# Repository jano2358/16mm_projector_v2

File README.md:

# 16mm_projector_v2
mod of a 16mm projector for the project "El curso del tiempo" from Xavi Hurtado

This is a modification of a projector (EIKI SSL0L) to take control over the parameters of the projection: tape speed, amount of light and shutter.
For the light we replace the incandescent bulb (300W, lumens: unknown)  by a COB LED (Citizen CLU058-1825C4-303M2K1, 100W about 17000 lumen).
To control the tape speed, We replaced the original motor with a DC brushless servo motor (Trinamic QBL5704-94-04-032 and TMCM-1630 control board).
The shutter originaly was hard linked to the main motor, we eliminated the hard link to have control independant, added a secondary shutter and two DC motors to move them. The link to the main motor and sync was made by a dual PLL system programed on an Arduino M0 board.
The power for these DC motors is delivered trough a Pololu board dual MC33296.
Arduino also controls the communication with the TMCM-1630 trough serial interface, the amount of light by switching the LED with a power
mosfet and receive the control from the computer over an ethernet line in OSC packets (we use here the Arduino Ethernet 2 Wiznet W5500).
The power is supplied by a Mean Well RSP-500-48 raised to 54V, with two DC-DC converters based on the TPS54560 chip from TI.

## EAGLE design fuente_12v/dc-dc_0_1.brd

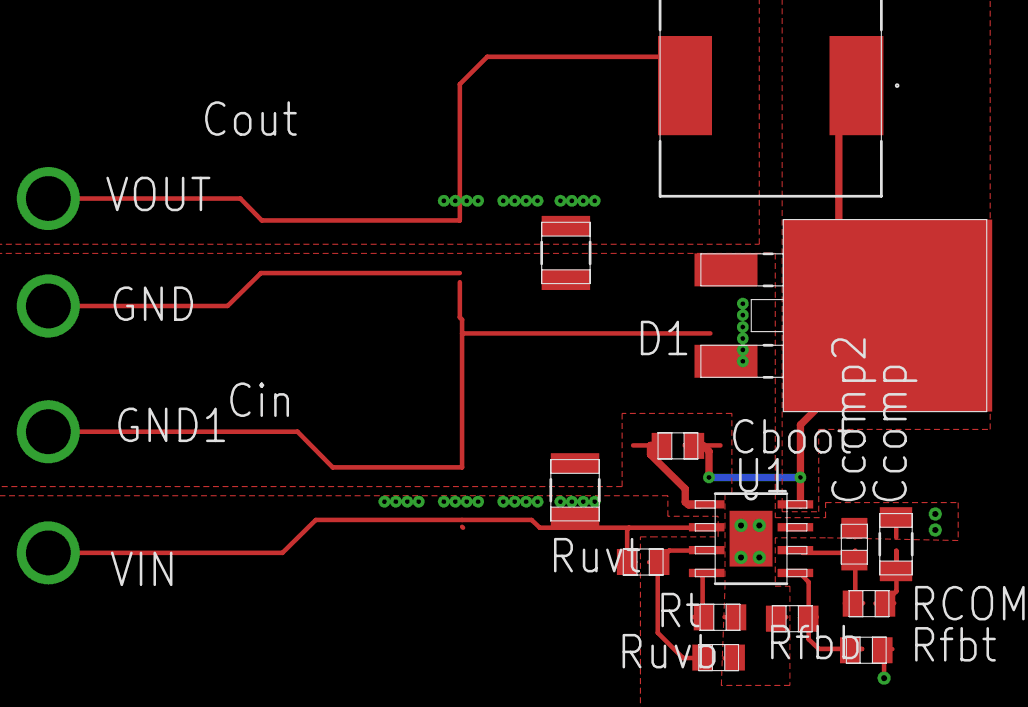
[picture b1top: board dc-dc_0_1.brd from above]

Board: 4 copper layers, 18 parts (0 on the bottom side), 10 nets.

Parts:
Cboot: 0805
Ccomp: 1206
Ccomp2: 0805
Cin: 1210
Cout: 1210_280
D1: DDPAK
GND, GND1: TP-1502
L1: MSS1210
RCOMP: 0805
Rfbb: 0805
Rfbt: 0805
Rt: 0805
Ruvb: 0805
Ruvt: 0805
U1: R-PDSO-G8
VIN: TP-1502
VOUT: TP-1502

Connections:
0: Ccomp.2, Ccomp2.2, Cin.2, Cout.2, D1.1, D1.3, GND.1, GND1.1, Rfbb.2, Rt.2, Ruvb.2, U1.7, U1.9
1: Ccomp2.1, RCOMP.2, U1.6
2: Rt.1, U1.4
3: Cboot.1, U1.1
4: Rfbb.1, Rfbt.2, U1.5
5: Cboot.2, D1.2, L1.1, U1.8
6: Cin.1, Ruvt.1, U1.2, VIN.1
7: Cout.1, L1.2, Rfbt.1, VOUT.1
20: Ccomp.1, RCOMP.1
29: Ruvb.1, Ruvt.2, U1.3

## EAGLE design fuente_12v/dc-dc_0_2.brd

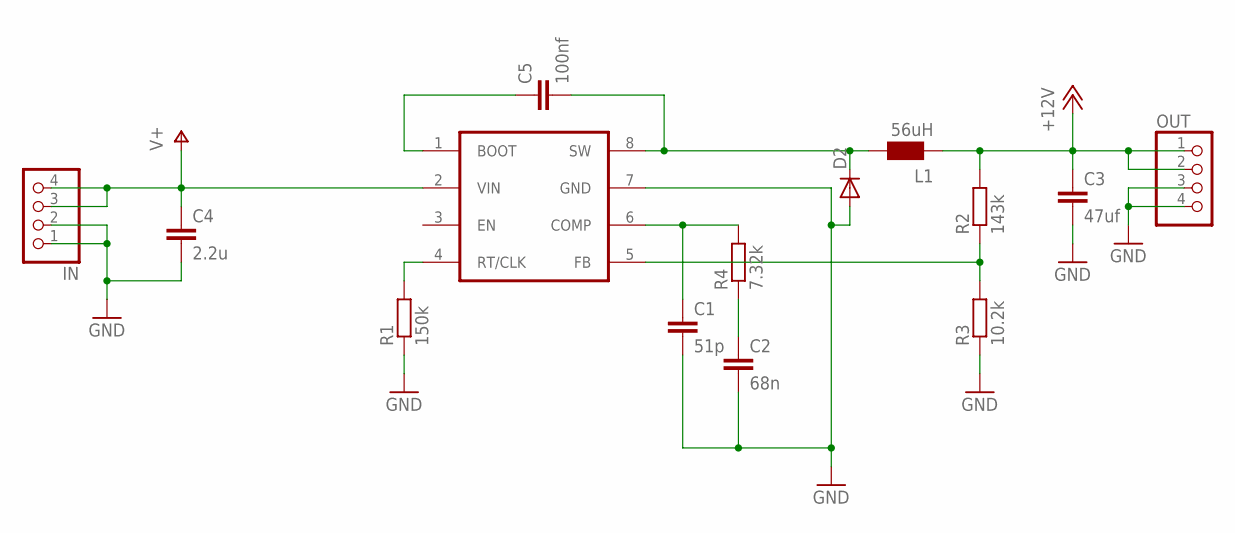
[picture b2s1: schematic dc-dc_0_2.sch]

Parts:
C1: 51p; C0805
C2: 68n; C1206
C3: 47uf; C1210
C4: 2.2u; C1210
C5: 100nf; C0805
D2: DIODE-DO-214AC; DO-214AC
IN: PINHD-1X4; 1X04
L1: 56uH; WE-PD_L/XL/XXL
OUT: PINHD-1X4; 1X04
R1: 150k; R0805
R2: 143k; R0805
R3: 10.2k; R0805
R4: 7.32k; R0805
U1: TPS54560; SO08-POWERPAD

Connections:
+12V: C3.1, L1.2 (1), OUT.1, OUT.2, R2.2
GND: C1.2, C2.2, C3.2, C4.2, D2.A, IN.1, IN.2, OUT.3, OUT.4, R1.1, R3.1, U1.7 (GND)
unnamed: C5.1, U1.1 (BOOT)
unnamed: C5.2, D2.C, L1.1 (2), U1.8 (SW)
unnamed: R2.1, R3.2, U1.5 (FB)
unnamed: C1.1, R4.2, U1.6 (COMP)
unnamed: C2.1, R4.1
unnamed: R1.2, U1.4 (RT/CLK)
V+: C4.1, IN.3, IN.4, U1.2 (VIN)

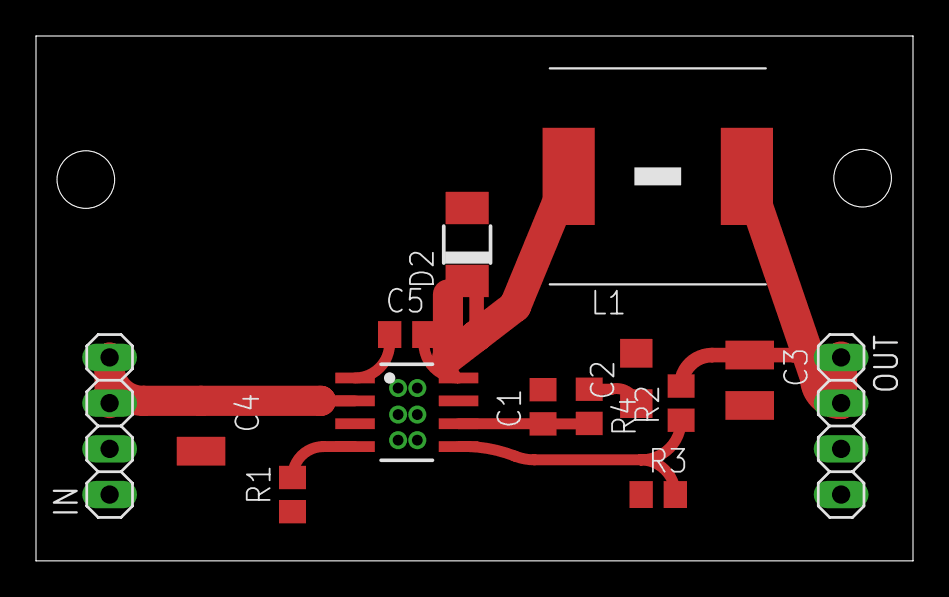
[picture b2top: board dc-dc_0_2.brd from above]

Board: 2 copper layers, 48.7 x 29.2 mm, 14 parts (0 on the bottom side), 9 nets.

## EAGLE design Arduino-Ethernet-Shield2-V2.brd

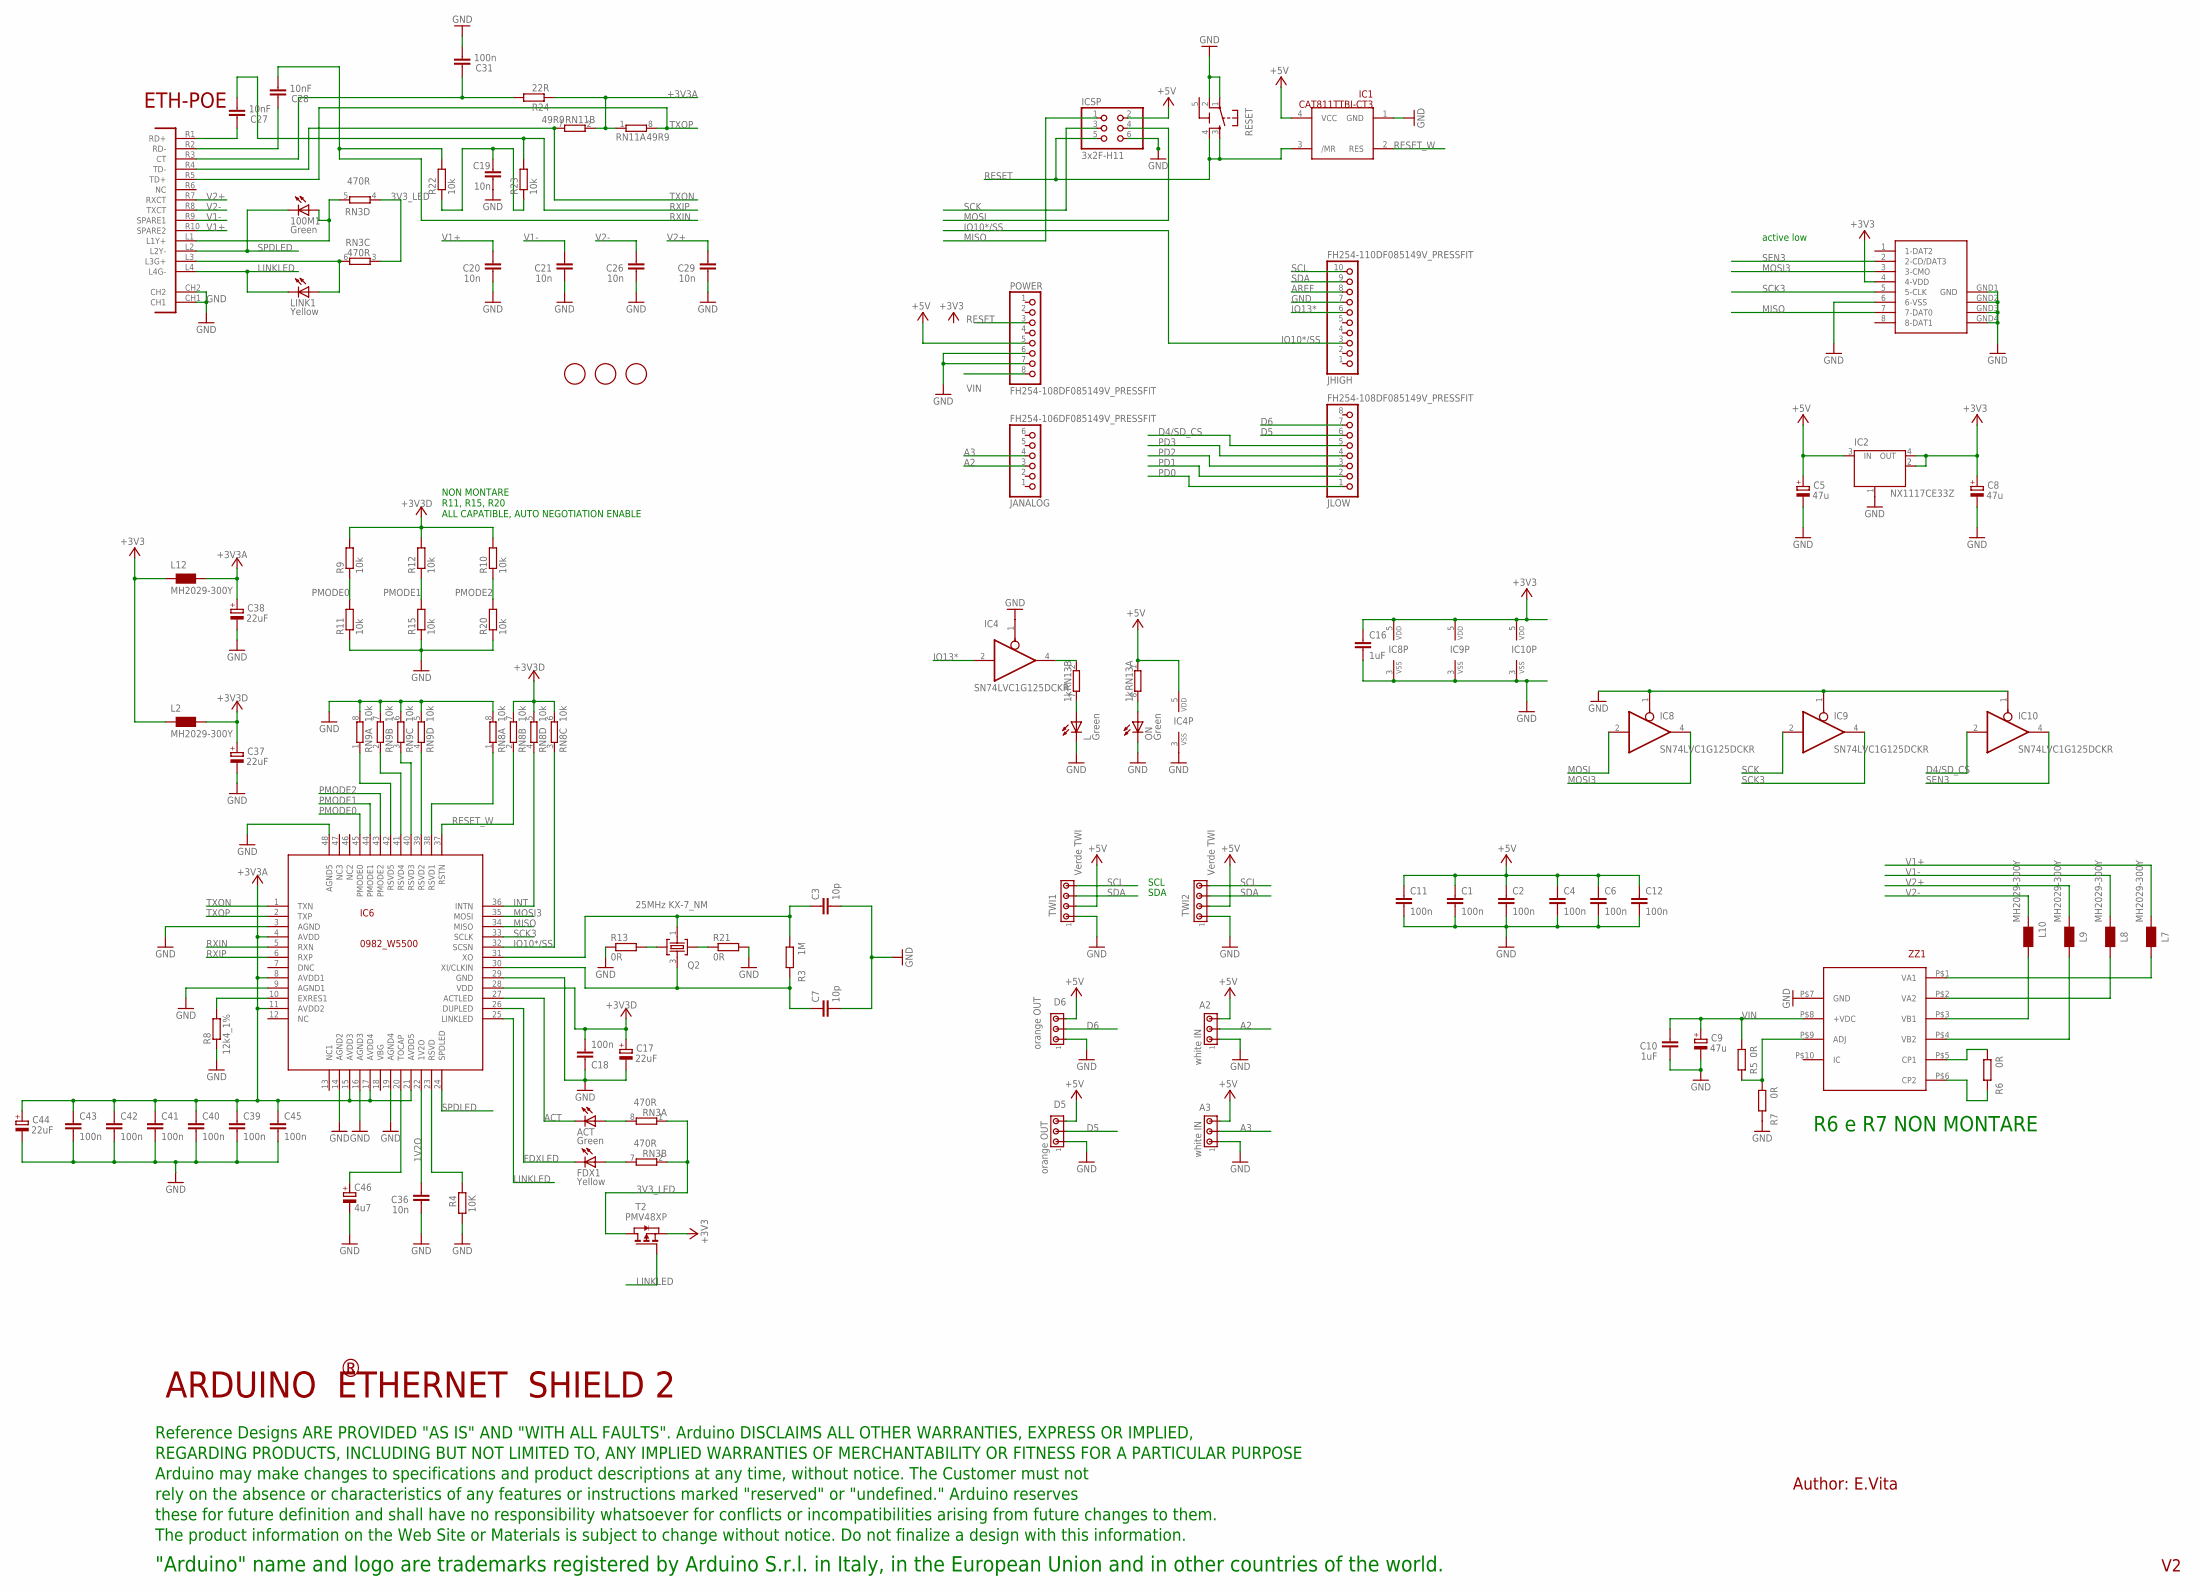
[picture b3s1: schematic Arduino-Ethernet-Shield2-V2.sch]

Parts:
100M1: Green; CHIPLED_0805
A2, A3: white IN; 10X03MTA
ACT: Green; CHIPLED_0805
C1, C2, C4, C6, C11, C12, C18, C31, C39, C40, C41, C42, C43, C45: 100n; C0603-ROUND
C3, C7: 10p; C0603-ROUND
C5, C8, C9: 47u; PANASONIC_D
C10, C16: 1uF; C0603-ROUND
C17, C37, C38, C44: 22uF; SMC_B
C19, C20, C21, C26, C29, C36: 10n; C0603-ROUND
C27, C28: 10nF; C0603-ROUND
C46: 4u7; SMC_A
D5, D6: orange OUT; 10X03MTA
FDX1: Yellow; CHIPLED_0805
FID2, FID3, FID4: FIDUCIALMOUNT; FIDUCIA-MOUNT
IC1: CAT811TTBI-CT3; SOT143
IC2: NX1117CE33Z; SOT223
IC4, IC8, IC9, IC10: SN74LVC1G125DCKR; SC70-5
IC6: 0982_W5500; TQFP48-7X7
ICSP: 3x2F-H11; 2X03
JANALOG: FH254-106DF085149V_PRESSFIT; 1X06-TH-PRESSFIT
JHIGH: FH254-110DF085149V_PRESSFIT; 1X10-TH-PRESSFIT
JLOW: FH254-108DF085149V_PRESSFIT; 1X08-TH-PRESSFIT
L: Green; CHIPLED_0805
L2, L7, L8, L9, L10, L12: MH2029-300Y; 0805
LINK1: Yellow; CHIPLED_0805
ON: Green; CHIPLED_0805
POWER: FH254-108DF085149V_PRESSFIT; 1X08-TH-PRESSFIT
Q2: 25MHz KX-7_NM; CRYSTAL3.2X2.5
R3: 1M; R0603-ROUND
R4: 10K; R0603-ROUND
R5, R6, R7: 0R; R0603-ROUND
R8: 12k4_1%; R0603-ROUND
R9, R10, R11, R12, R15, R20, R22, R23: 10k; R0603-ROUND
R13, R21: 0R; R0402
R24: 22R; R0603-ROUND
RESET: 0946_TS42031-160W-TR-7260; TS42
RN3: 470R; CAY16
RN8, RN9: 10k; CAY16
RN11: 49R9; CAY16
RN13: 1k; CAY16
T2: PMV48XP; SOT-23; PART_NUMBER PMV48XP
TWI1, TWI2: Verde TWI; 10X04MTA
U$1: DISCLAIMER
UC1: RB1-125BHQ1A; POE-RJ45
X1: 0046_15TW-882; SDCARD-15TW-8821
ZZ1: 0343_AG9612-2BR; AG9000

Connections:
1V2O: C36.2, IC6.22 (1V2O)
3V3_LED: RN3.1, RN3.2 (1), RN3.3 (1), RN3.4 (1), T2.1 (D)
5-GND: RESET.5 (5-GND)
+3V3: C8.+, C16.1, IC2.2 (OUT), IC2.4 (OUT), IC8.5 (VDD), IC9.5 (VDD), IC10.5 (VDD), L2.1, L12.1, T2.2 (S), X1.4 (4-VDD)
+3V3A: C38.+, C39.1, C40.1, C41.1, C42.1, C43.1, C44.+, C45.1, IC6.4 (AVDD), IC6.8 (AVDD1), IC6.11 (AVDD2), IC6.15 (AVDD3), IC6.17 (AVDD4), IC6.21 (AVDD5), L12.2, R24.1, RN11.1, RN11.2 (1)
+3V3D: C17.+, C18.2, C37.+, IC6.28 (VDD), L2.2, R9.2, R10.2, R12.2, RN8.5 (2), RN8.6 (2), RN8.7 (2)
+5V: A2.3, A3.3, C1.1, C2.1, C4.1, C5.+, C6.1, C11.1, C12.1, D5.3, D6.3, IC1.4 (VCC), IC2.3 (IN), IC4.5 (VDD), ICSP.2, POWER.5, RN13.1, TWI1.2, TWI2.2
A2: A2.2, JANALOG.3
A3: A3.2, JANALOG.4
ACT: ACT.C, IC6.27 (ACTLED)
AREF: JHIGH.8
D4/SD_CS: IC10.2 (I), JLOW.5
D5: D5.2, JLOW.6
D6: D6.2, JLOW.7
FDXLED: FDX1.C, IC6.26 (DUPLED)
GND: A2.1, A3.1, C1.2, C2.2, C3.2, C4.2, C5.-, C6.2, C7.2, C8.-, C9.-, C10.1, C11.2, C12.2, C16.2, C17.-, C18.1, C19.1, C20.1, C21.1, C26.1, C29.1, C31.1, C36.1, C37.-, C38.-, C39.2, C40.2, C41.2, C42.2, C43.2, C44.-, C45.2, C46.-, D5.1, D6.1, IC1.1 (GND), IC2.1 (GND/ADJ), IC4.1 (OE), IC4.3 (VSS), IC6.3 (AGND), IC6.9 (AGND1), IC6.14 (AGND2), IC6.16 (AGND3), IC6.19 (AGND4), IC6.29 (GND), IC6.48 (AGND5), IC8.1 (OE), IC8.3 (VSS), IC9.1 (OE), IC9.3 (VSS), IC10.1 (OE), IC10.3 (VSS), ICSP.6, JHIGH.7, L.C, ON.C, POWER.6, POWER.7, R4.1, R7.2, R8.1, R11.1, R13.1, R15.1, R20.1, R21.2, RESET.1, RESET.2, RN8.8 (2), RN9.5 (2), RN9.6 (2), RN9.7 (2), RN9.8 (2), TWI1.1, TWI2.1, UC1.CH1, UC1.CH2, X1.6 (6-VSS), X1.GND1 (GND), X1.GND2 (GND1), X1.GND3 (GND2), X1.GND4 (GND3), ZZ1.P$7 (GND)
INT: IC6.36 (INTN), RN8.4 (1)
IO10*/SS: IC6.32 (SCSN), JHIGH.3, RN8.3 (1)
IO13*: IC4.2 (I), JHIGH.6
LINKLED: IC6.25 (LINKLED), LINK1.C, T2.3 (G), UC1.L4 (L4G-)
MISO: IC6.34 (MISO), ICSP.1, X1.7 (7-DAT0)
MOSI: IC8.2 (I), ICSP.4
MOSI3: IC6.35 (MOSI), IC8.4 (O), X1.3 (3-CMO)
unnamed: L7.2, ZZ1.P$1 (VA1)
unnamed: L8.2, ZZ1.P$2 (VA2)
unnamed: L9.2, ZZ1.P$4 (VB2)
unnamed: L10.2, ZZ1.P$3 (VB1)
unnamed: C3.1, IC6.31 (XO), Q2.1, R3.1
unnamed: IC6.39 (RSVD2), RN9.4 (1)
unnamed: ACT.A, RN3.8 (2)
unnamed: Q2.2, R13.2
unnamed: Q2.4, R21.1
unnamed: LINK1.A, RN3.6 (2), UC1.L3 (L3G+)
unnamed: IC6.23 (RSVD), R4.2
unnamed: 100M1.A, RN3.5 (2), UC1.L1 (L1Y+)
unnamed: C19.2, R22.1, R23.1
unnamed: C27.2, UC1.R1 (RD+)
unnamed: C28.2, UC1.R2 (RD-)
unnamed: FDX1.A, RN3.7 (2)
unnamed: IC6.40 (RSVD3), RN9.3 (1)
unnamed: R6.1, ZZ1.P$5 (CP1)
unnamed: R6.2, ZZ1.P$6 (CP2)
unnamed: R5.2, R7.1, ZZ1.P$9 (ADJ)
unnamed: IC6.41 (RSVD4), RN9.2 (1)
unnamed: C31.2, R24.2, UC1.R3 (CT)
unnamed: IC6.42 (RSVD5), RN9.1
unnamed: C46.+, IC6.20 (TOCAP)
unnamed: IC6.38 (RSVD1), RN8.1
unnamed: IC6.10 (EXRES1), R8.2
unnamed: ON.A, RN13.8 (2)
unnamed: IC4.4 (O), RN13.2 (1)
unnamed: L.A, RN13.7 (2)
NC: IC6.12 (NC)
OSC2E2: C7.1, IC6.30 (XI/CLKIN), Q2.3, R3.2
PD0: JLOW.1
PD1: JLOW.2
PD2: JLOW.3
PD3: JLOW.4
PMODE0: IC6.45 (PMODE0), R9.1, R11.2
PMODE1: IC6.44 (PMODE1), R12.1, R15.2
PMODE2: IC6.43 (PMODE2), R10.1, R20.2
RESET: IC1.3 (/MR), ICSP.5, POWER.3, RESET.3, RESET.4
RESET_W: IC1.2 (RES), IC6.37 (RSTN), RN8.2 (1)
RXIN: C28.1, IC6.5 (RXN), R22.2
RXIP: C27.1, IC6.6 (RXP), R23.2
SCK: IC9.2 (I), ICSP.3
SCK3: IC6.33 (SCLK), IC9.4 (O), X1.5 (5-CLK)
SCL: JHIGH.10, TWI1.4, TWI2.4
SDA: JHIGH.9, TWI1.3, TWI2.3
SEN3: IC10.4 (O), X1.2 (2-CD/DAT3)
SPDLED: 100M1.C, IC6.24 (SPDLED), UC1.L2 (L2Y-)
TXON: IC6.1 (TXN), RN11.7 (2), UC1.R4 (TD-)
TXOP: IC6.2 (TXP), RN11.8 (2), UC1.R5 (TD+)
V1+: C20.2, L7.1, UC1.R10 (SPARE2)
V1-: C21.2, L8.1, UC1.R9 (SPARE1)
V2+: C29.2, L9.1, UC1.R7 (RXCT)
V2-: C26.2, L10.1, UC1.R8 (TXCT)
VIN: C9.+, C10.2, POWER.8, R5.1, ZZ1.P$8 (+VDC)

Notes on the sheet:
active low
NON MONTARE R11, R15, R20 ALL CAPATIBLE, AUTO NEGOTIATION ENABLE
ETH-POE
SCL
SDA
R6 e R7 NON MONTARE
ARDUINO ETHERNET SHIELD 2
Author: E.Vita

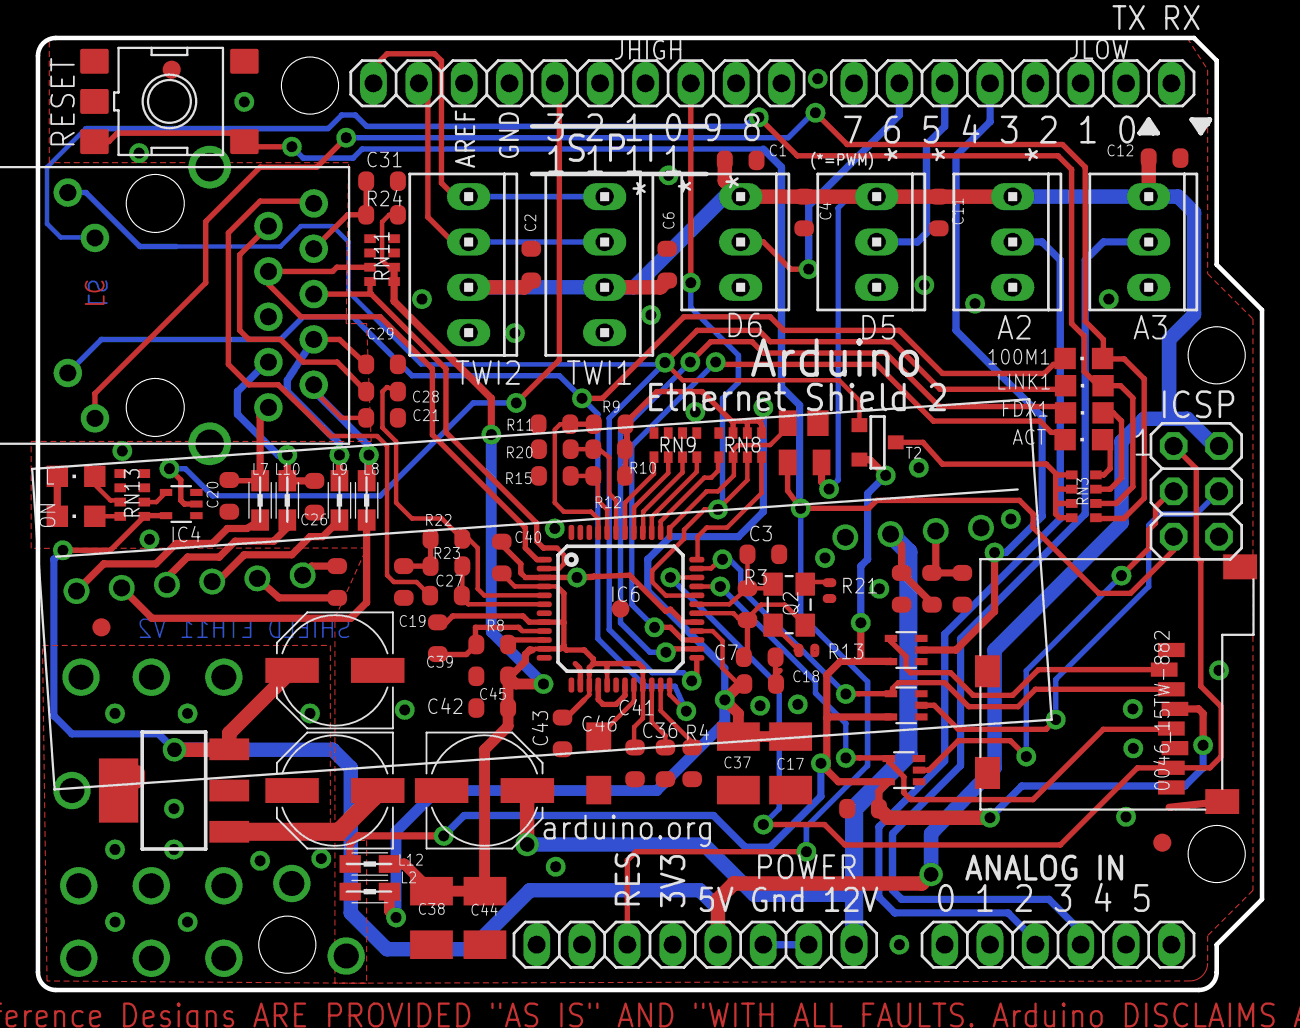
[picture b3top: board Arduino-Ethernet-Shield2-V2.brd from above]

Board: 2 copper layers, 68.6 x 53.3 mm, 96 parts (0 on the bottom side), 71 nets.

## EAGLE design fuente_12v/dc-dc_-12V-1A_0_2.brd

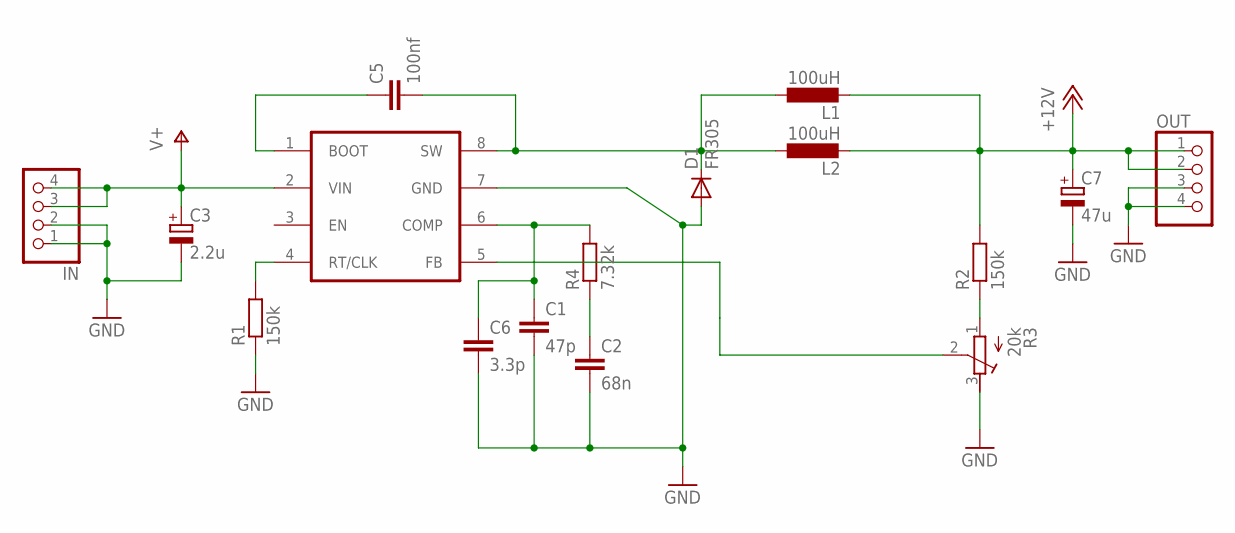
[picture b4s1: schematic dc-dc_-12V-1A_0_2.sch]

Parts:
C1: 47p; C1206
C2: 68n; C1206
C3: 2.2u; E2-4
C5: 100nf; C0805
C6: 3.3p; C1206
C7: 47u; E2-4
D1: FR305; DO201-15
IN: PINHD-1X4; 1X04
L1, L2: 100uH; RCL_6000-XXXX-RC
OUT: PINHD-1X4; 1X04
R1, R2: 150k; R0805
R3: 20k; RTRIM64X
R4: 7.32k; 0204/5
U1: TPS54560; SO08-POWERPAD

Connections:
+12V: C7.+, L1.2, L2.2, OUT.1, OUT.2, R2.2
GND: C1.2, C2.2, C3.-, C6.2, C7.-, D1.A, IN.1, IN.2, OUT.3, OUT.4, R1.1, R3.3 (A), U1.7 (GND)
unnamed: C5.1, U1.1 (BOOT)
unnamed: C5.2, D1.C, L1.1, L2.1, U1.8 (SW)
unnamed: R2.1, R3.1 (E)
unnamed: R3.2 (S), U1.5 (FB)
unnamed: C1.1, C6.1, R4.2, U1.6 (COMP)
unnamed: C2.1, R4.1
unnamed: R1.2, U1.4 (RT/CLK)
V+: C3.+, IN.3, IN.4, U1.2 (VIN)

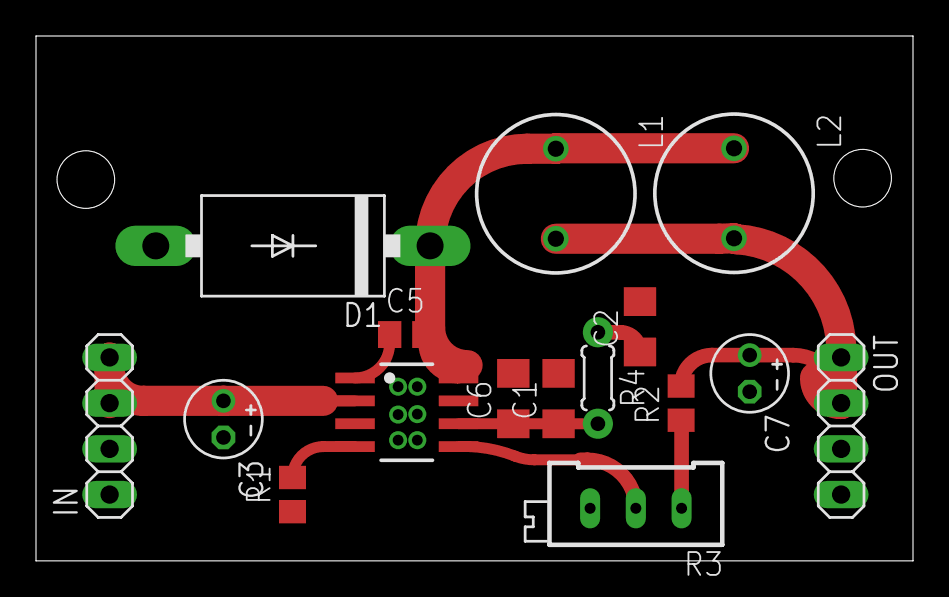
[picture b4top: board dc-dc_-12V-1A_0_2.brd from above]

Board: 2 copper layers, 48.7 x 29.2 mm, 16 parts (0 on the bottom side), 10 nets.

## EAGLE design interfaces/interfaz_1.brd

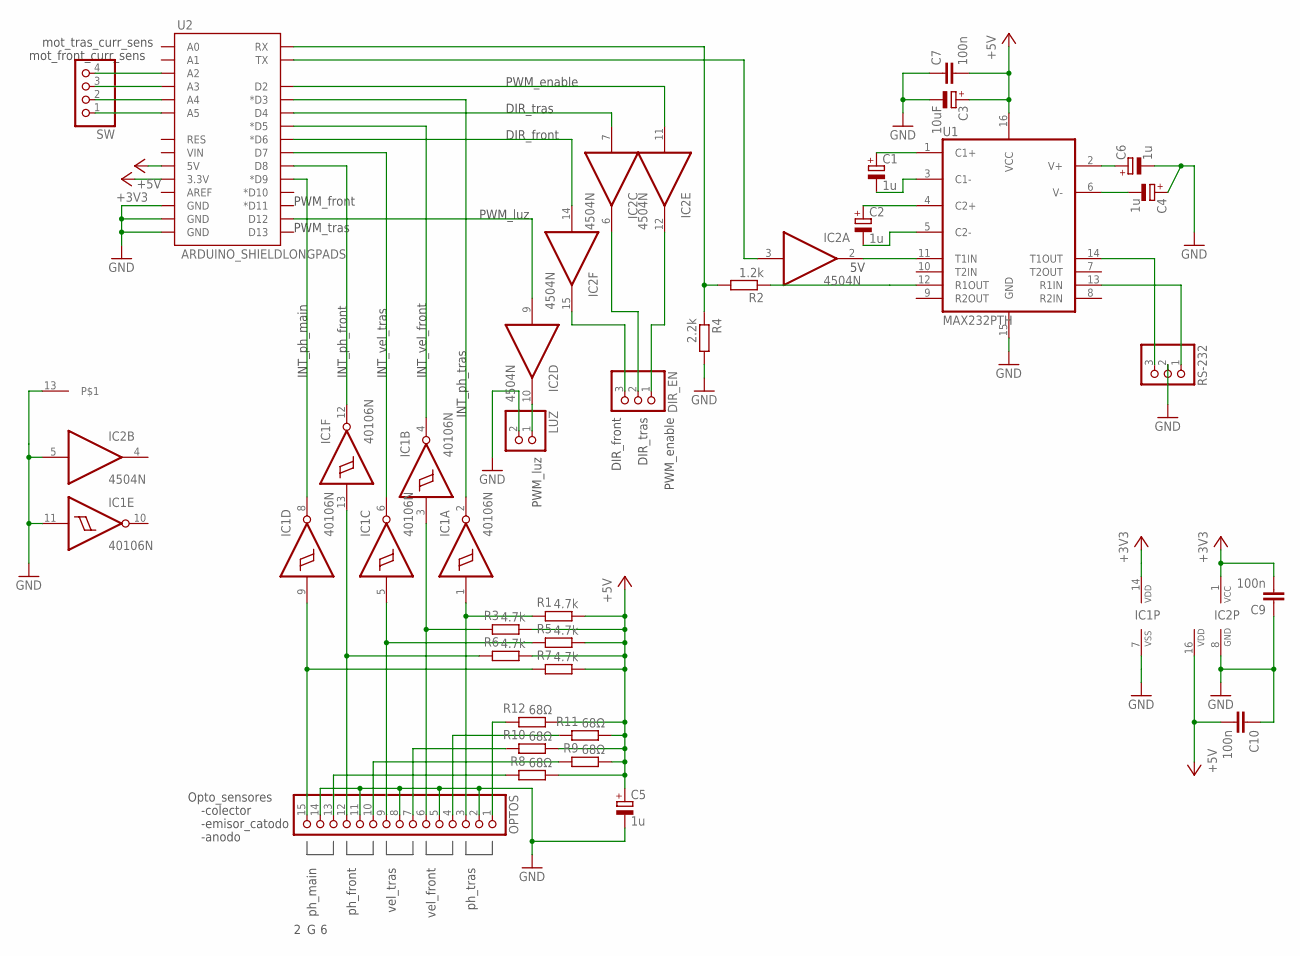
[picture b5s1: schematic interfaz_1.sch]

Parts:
C1, C2, C4, C5, C6: 1u; E2-4
C3: 10uF; E2-4
C7, C9, C10: 100n; C025-025X050
DIR_EN: PINHD-1X3; 1X03
IC1: 40106N; DIL14
IC2: 4504N; DIL16
LUZ: PINHD-1X2; 1X02
OPTOS: PINHD-1X15; 1X15
R1, R3, R5, R6, R7: 4.7k; 0204/5
R2: 1.2k; 0204/5
R4: 2.2k; 0204/5
R8, R9, R10, R11, R12: 68Ω; 0204/5
RS-232: PINHD-1X3; 1X03
SW: PINHD-1X4; 1X04
U1: MAX232PTH; DIL16
U2: ARDUINO_SHIELDLONGPADS; DUEMILANOVE_SHIELD_LONGPADS

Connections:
+3V3: C9.2, IC1.14 (VDD), IC2.1 (VCC), U2.3.3V
+5V: C3.+, C5.+, C7.2, C10.2, IC2.16 (VDD), R1.1, R3.1, R5.1, R6.1, R7.1, R8.1, R9.1, R10.1, R11.1, R12.1, U1.16 (VCC), U2.5V
GND: C3.-, C4.+, C5.-, C6.-, C7.1, C9.1, C10.1, IC1.7 (VSS), IC1.11 (I), IC2.5 (I), IC2.8 (GND), IC2.13, LUZ.2, OPTOS.2, OPTOS.5, OPTOS.8, OPTOS.11, OPTOS.14, R4.2, RS-232.2, U1.15 (GND), U2.GND@0 (GND), U2.GND@1 (GND), U2.GND@2 (GND)
unnamed: C1.+, U1.1 (C1+)
unnamed: C1.-, U1.3 (C1-)
unnamed: C2.+, U1.4 (C2+)
unnamed: C2.-, U1.5 (C2-)
unnamed: C4.-, U1.6 (V-)
unnamed: C6.+, U1.2 (V+)
unnamed: RS-232.1, U1.13 (R1IN)
unnamed: IC2.11 (I), U2.D2
unnamed: IC2.3 (I), U2.TX
unnamed: R2.1, U1.12 (R1OUT)
unnamed: R2.2, R4.1, U2.RX
unnamed: IC2.2 (O), U1.11 (T1IN)
unnamed: DIR_EN.1, IC2.12 (O)
unnamed: RS-232.3, U1.14 (T1OUT)
unnamed: IC2.7 (I), U2.D4
unnamed: DIR_EN.2, IC2.6 (O)
unnamed: IC2.14 (I), U2.D6 (*D6)
unnamed: DIR_EN.3, IC2.15 (O)
unnamed: IC2.9 (I), U2.D12
unnamed: IC2.10 (O), LUZ.1
unnamed: IC1.3 (I), OPTOS.6, R3.2
unnamed: IC1.2 (O), U2.D3 (*D3)
unnamed: IC1.4 (O), U2.D5 (*D5)
unnamed: IC1.6 (O), U2.D7
unnamed: IC1.12 (O), U2.D8
unnamed: IC1.8 (O), U2.D9 (*D9)
unnamed: IC1.1 (I), OPTOS.3, R1.2
unnamed: IC1.5 (I), OPTOS.9, R5.2
unnamed: IC1.13 (I), OPTOS.12, R6.2
unnamed: IC1.9 (I), OPTOS.15, R7.2
unnamed: OPTOS.13, R8.2
unnamed: OPTOS.10, R9.2
unnamed: OPTOS.7, R10.2
unnamed: OPTOS.4, R11.2
unnamed: OPTOS.1, R12.2
unnamed: SW.1, U2.A5
unnamed: SW.2, U2.A4
unnamed: SW.3, U2.A3
unnamed: SW.4, U2.A2

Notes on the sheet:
PWM_enable
DIR_tras
DIR_front
PWM_luz
PWM_tras
PWM_front
INT_vel_tras
INT_vel_front
INT_ph_tras
INT_ph_front
INT_ph_main
Opto_sensores
-colector
-emisor_catodo
-anodo
ph_main
ph_front
ph_tras
vel_front
vel_tras
mot_tras_curr_sens
mot_front_curr_sens

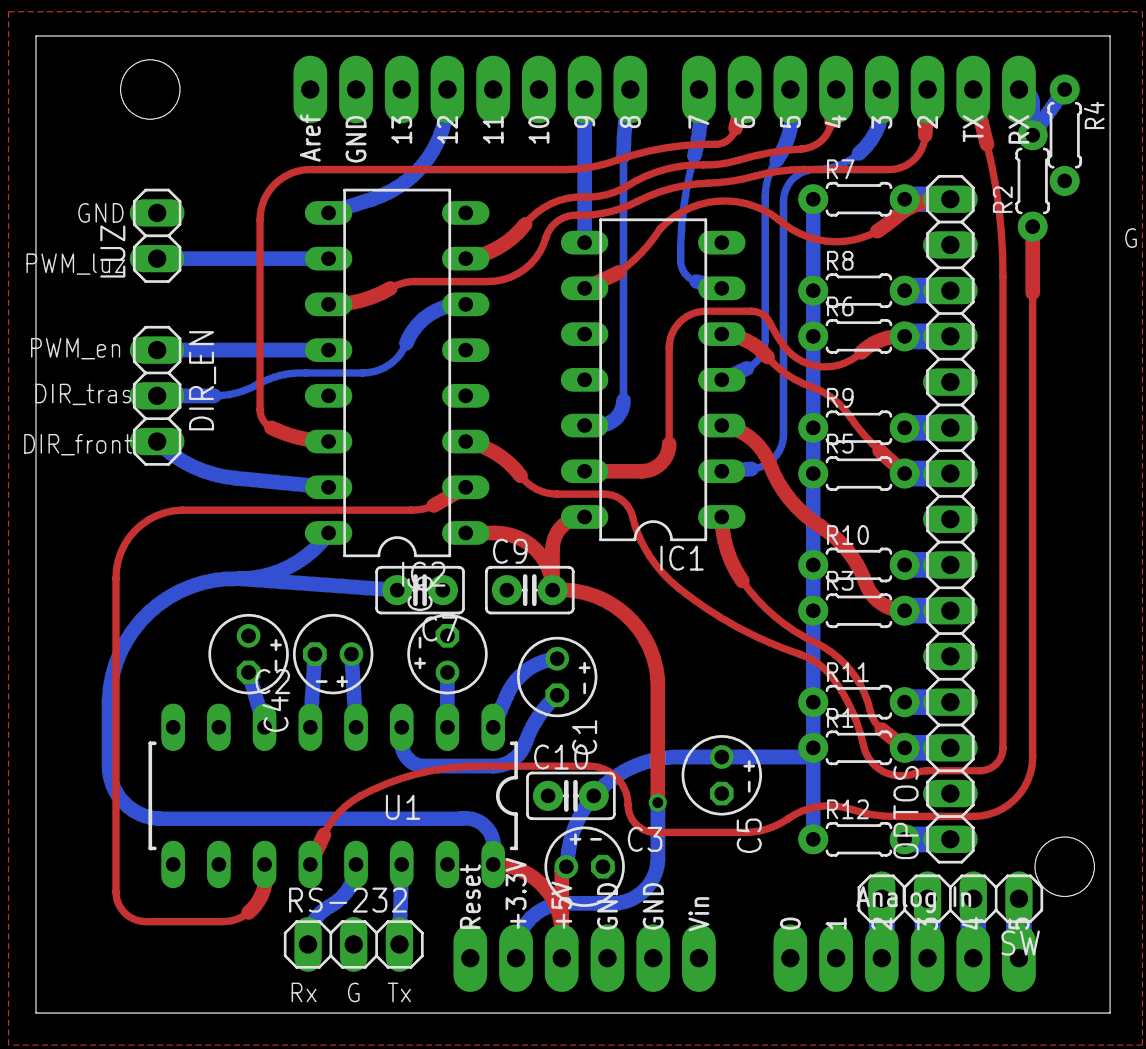
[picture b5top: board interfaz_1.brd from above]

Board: 2 copper layers, 59.7 x 54.3 mm, 30 parts (0 on the bottom side), 42 nets.

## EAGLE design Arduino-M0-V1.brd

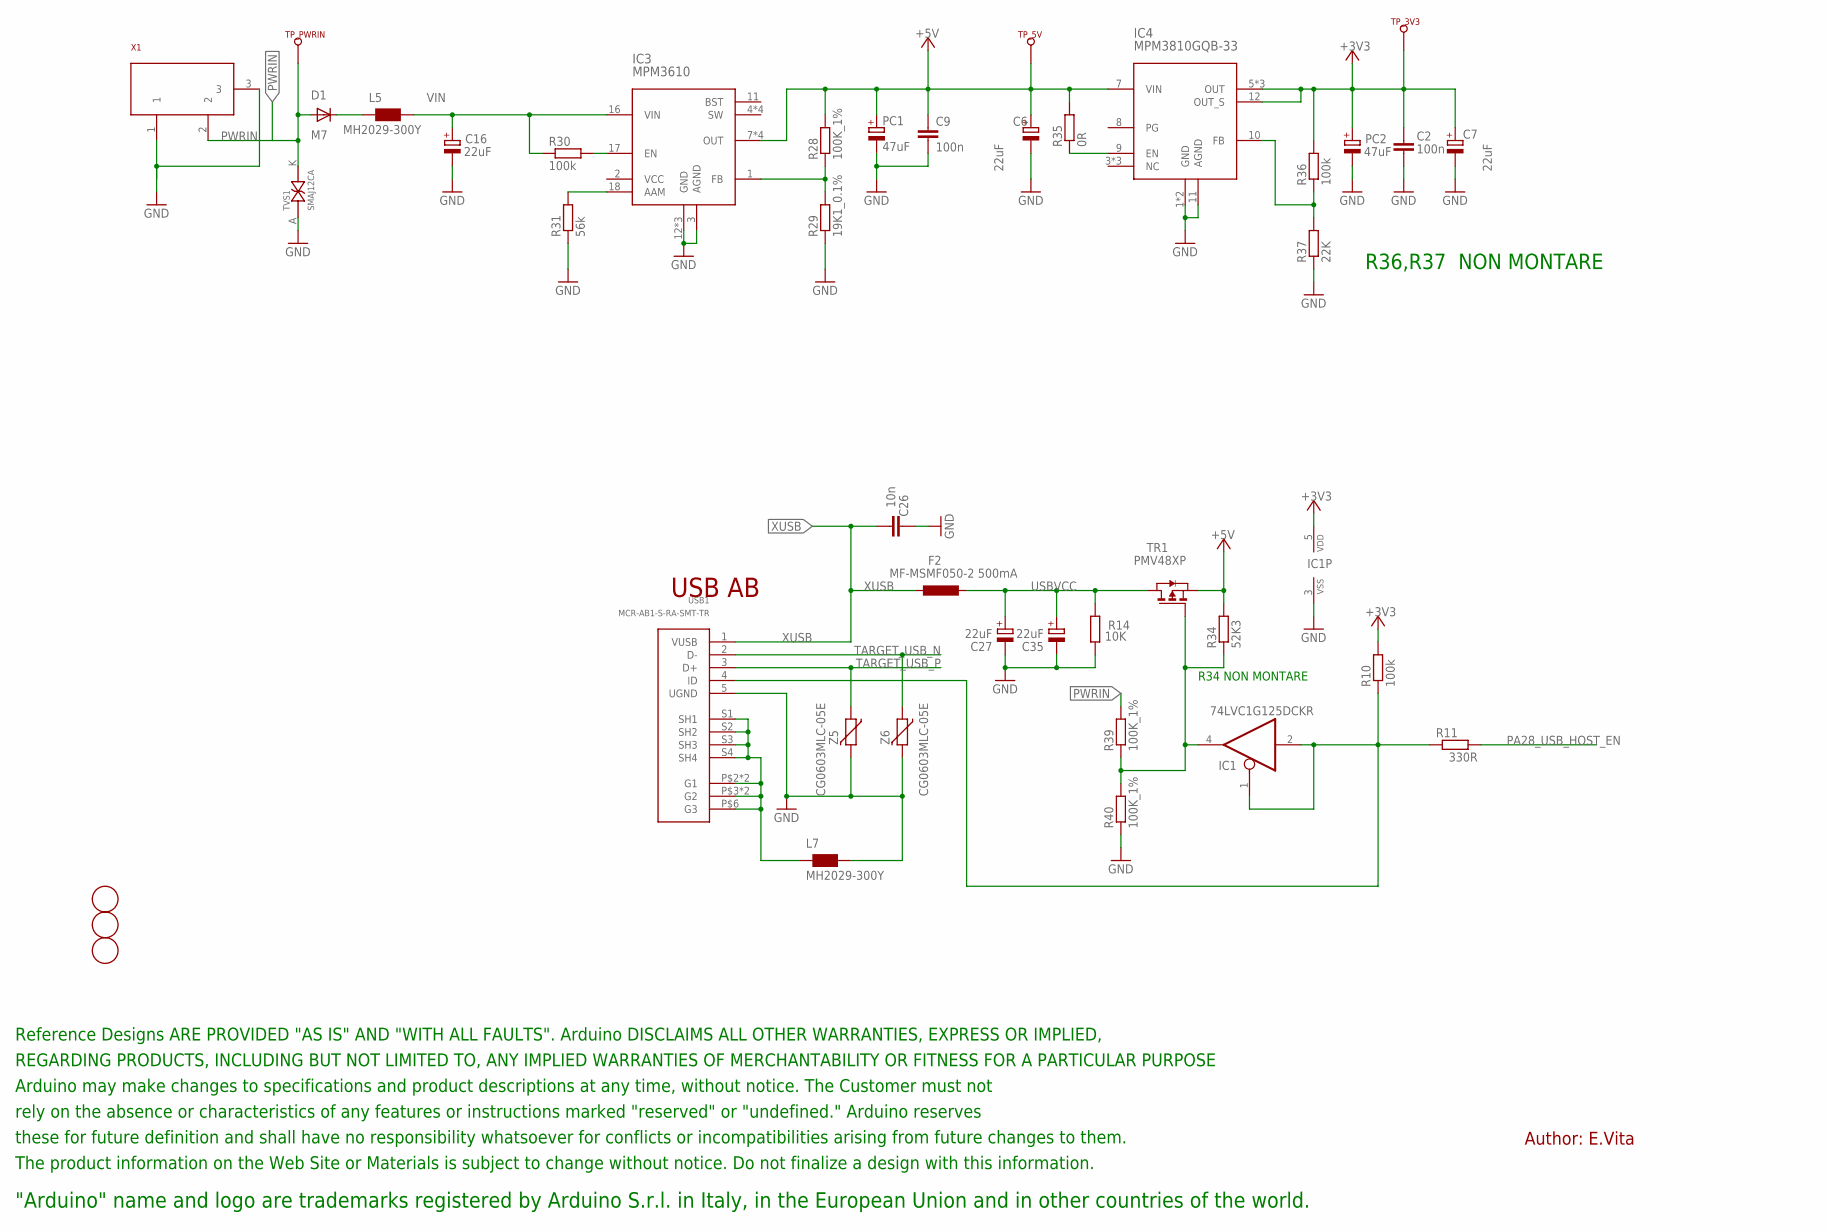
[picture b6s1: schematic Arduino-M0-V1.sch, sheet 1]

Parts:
C2, C9: 100n; C0603-ROUND
C6, C7, C16, C27, C35: 22uF; SMC_B
C26: 10n; C0603-ROUND
D1: M7; SMB
F2: MF-MSMF050-2 500mA; L1812
FD1, FD2, FD3: FIDUCIALMOUNT; FIDUCIA-MOUNT
IC1: 74LVC1G125DCKR; SC70-5
IC3: MPM3610; QFN-20
IC4: MPM3810GQB-33; QFN-12
L5, L7: MH2029-300Y; 0805
PC1, PC2: 47uF; PANASONIC_D
R10, R30, R36: 100k; R0603-ROUND
R11: 330R; R0603-ROUND
R14: 10K; R0603-ROUND
R28, R39, R40: 100K_1%; R0603-ROUND
R29: 19K1_0.1%; R0603-ROUND
R31: 56k; R0603-ROUND
R34: 52K3; R0603-ROUND
R35: 0R; R0603-ROUND
R37: 22K; R0603-ROUND
TP_3V3, TP_5V: TP_SP; TP-SP
TP_PWRIN: TP_SP; TP-SP
TR1: PMV48XP; SOT-23
TVS1: SMAJ12CA; SMA-TVS
U$1: DISCLAIMER-SMALL; DISCLAIMER
USB1: MCR-AB1-S-RA-SMT-TR; MCR-AB1-S-RA-SMT-SINGLHOLES
X1: 0018_19746-POWER-SUPPLY; POWERSUPPLY_DC-21MM
Z5, Z6: CG0603MLC-05E; CT/CN0603

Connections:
+3V3: C2.2, C7.+, IC1.5 (VDD), IC4.5 (OUT), IC4.6 (OUT), IC4.12 (OUT_S), IC4.14 (OUT), PC2.+, R10.2, R36.2, TP_3V3.X; also elsewhere on the board
+5V: C6.+, C9.1, IC3.7 (OUT), IC3.8 (OUT), IC3.9 (OUT), IC3.20 (OUT), IC4.7 (VIN), PC1.+, R28.2, R34.2, R35.2, TP_5V.X, TR1.2 (S); also elsewhere on the board
GND: C2.1, C6.-, C7.-, C9.2, C16.-, C26.2, C27.-, C35.-, IC1.3 (VSS), IC3.3 (AGND), IC3.12 (GND), IC3.13 (GND), IC3.14 (GND), IC4.1 (GND), IC4.2 (GND), IC4.11 (AGND), L7.2, PC1.-, PC2.-, R14.1, R29.1, R31.1, R37.1, R40.1, TVS1.A (AK), USB1.5 (UGND), X1.1, X1.3, Z5.2, Z6.2; also elsewhere on the board
unnamed: IC1.4 (O), R34.1, R39.1, R40.2, TR1.3 (G)
unnamed: IC1.1 (OE), IC1.2 (I), R10.1, R11.1, USB1.4 (ID)
unnamed: D1.C, L5.1
unnamed: IC4.9 (EN), R35.1
unnamed: IC4.10 (FB), R36.1, R37.2
unnamed: L7.1, USB1.P$2 (G1), USB1.P$3 (G2), USB1.P$6 (G3), USB1.P$8 (G1), USB1.P$10 (G2), USB1.S1 (SH1), USB1.S2 (SH2), USB1.S3 (SH3), USB1.S4 (SH4)
unnamed: IC3.1 (FB), R28.1, R29.2
unnamed: IC3.17 (EN), R30.2
unnamed: IC3.18 (AAM), R31.2
PA28_USB_HOST_EN: R11.2; also elsewhere on the board
PWRIN: D1.A, R39.2, TP_PWRIN.X, TVS1.K (KA), X1.2; also elsewhere on the board
TARGET_USB_N: USB1.2 (D-), Z6.1; also elsewhere on the board
TARGET_USB_P: USB1.3 (D+), Z5.1; also elsewhere on the board
USBVCC: C27.+, C35.+, F2.1, R14.2, TR1.1 (D)
VIN: C16.+, IC3.16 (VIN), L5.2, R30.1
XUSB: C26.1, F2.2, USB1.1 (VUSB)

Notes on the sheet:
USB AB
R34 NON MONTARE
R36,R37 NON MONTARE
Author: E.Vita

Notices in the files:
parts and their libraries:
wuerth-elektronik: Copyright: Würth Elektronik eiSos
SparkFun: Licensing: CC v3.0 Share-Alike You are welcome to use this library for commercial purposes.
